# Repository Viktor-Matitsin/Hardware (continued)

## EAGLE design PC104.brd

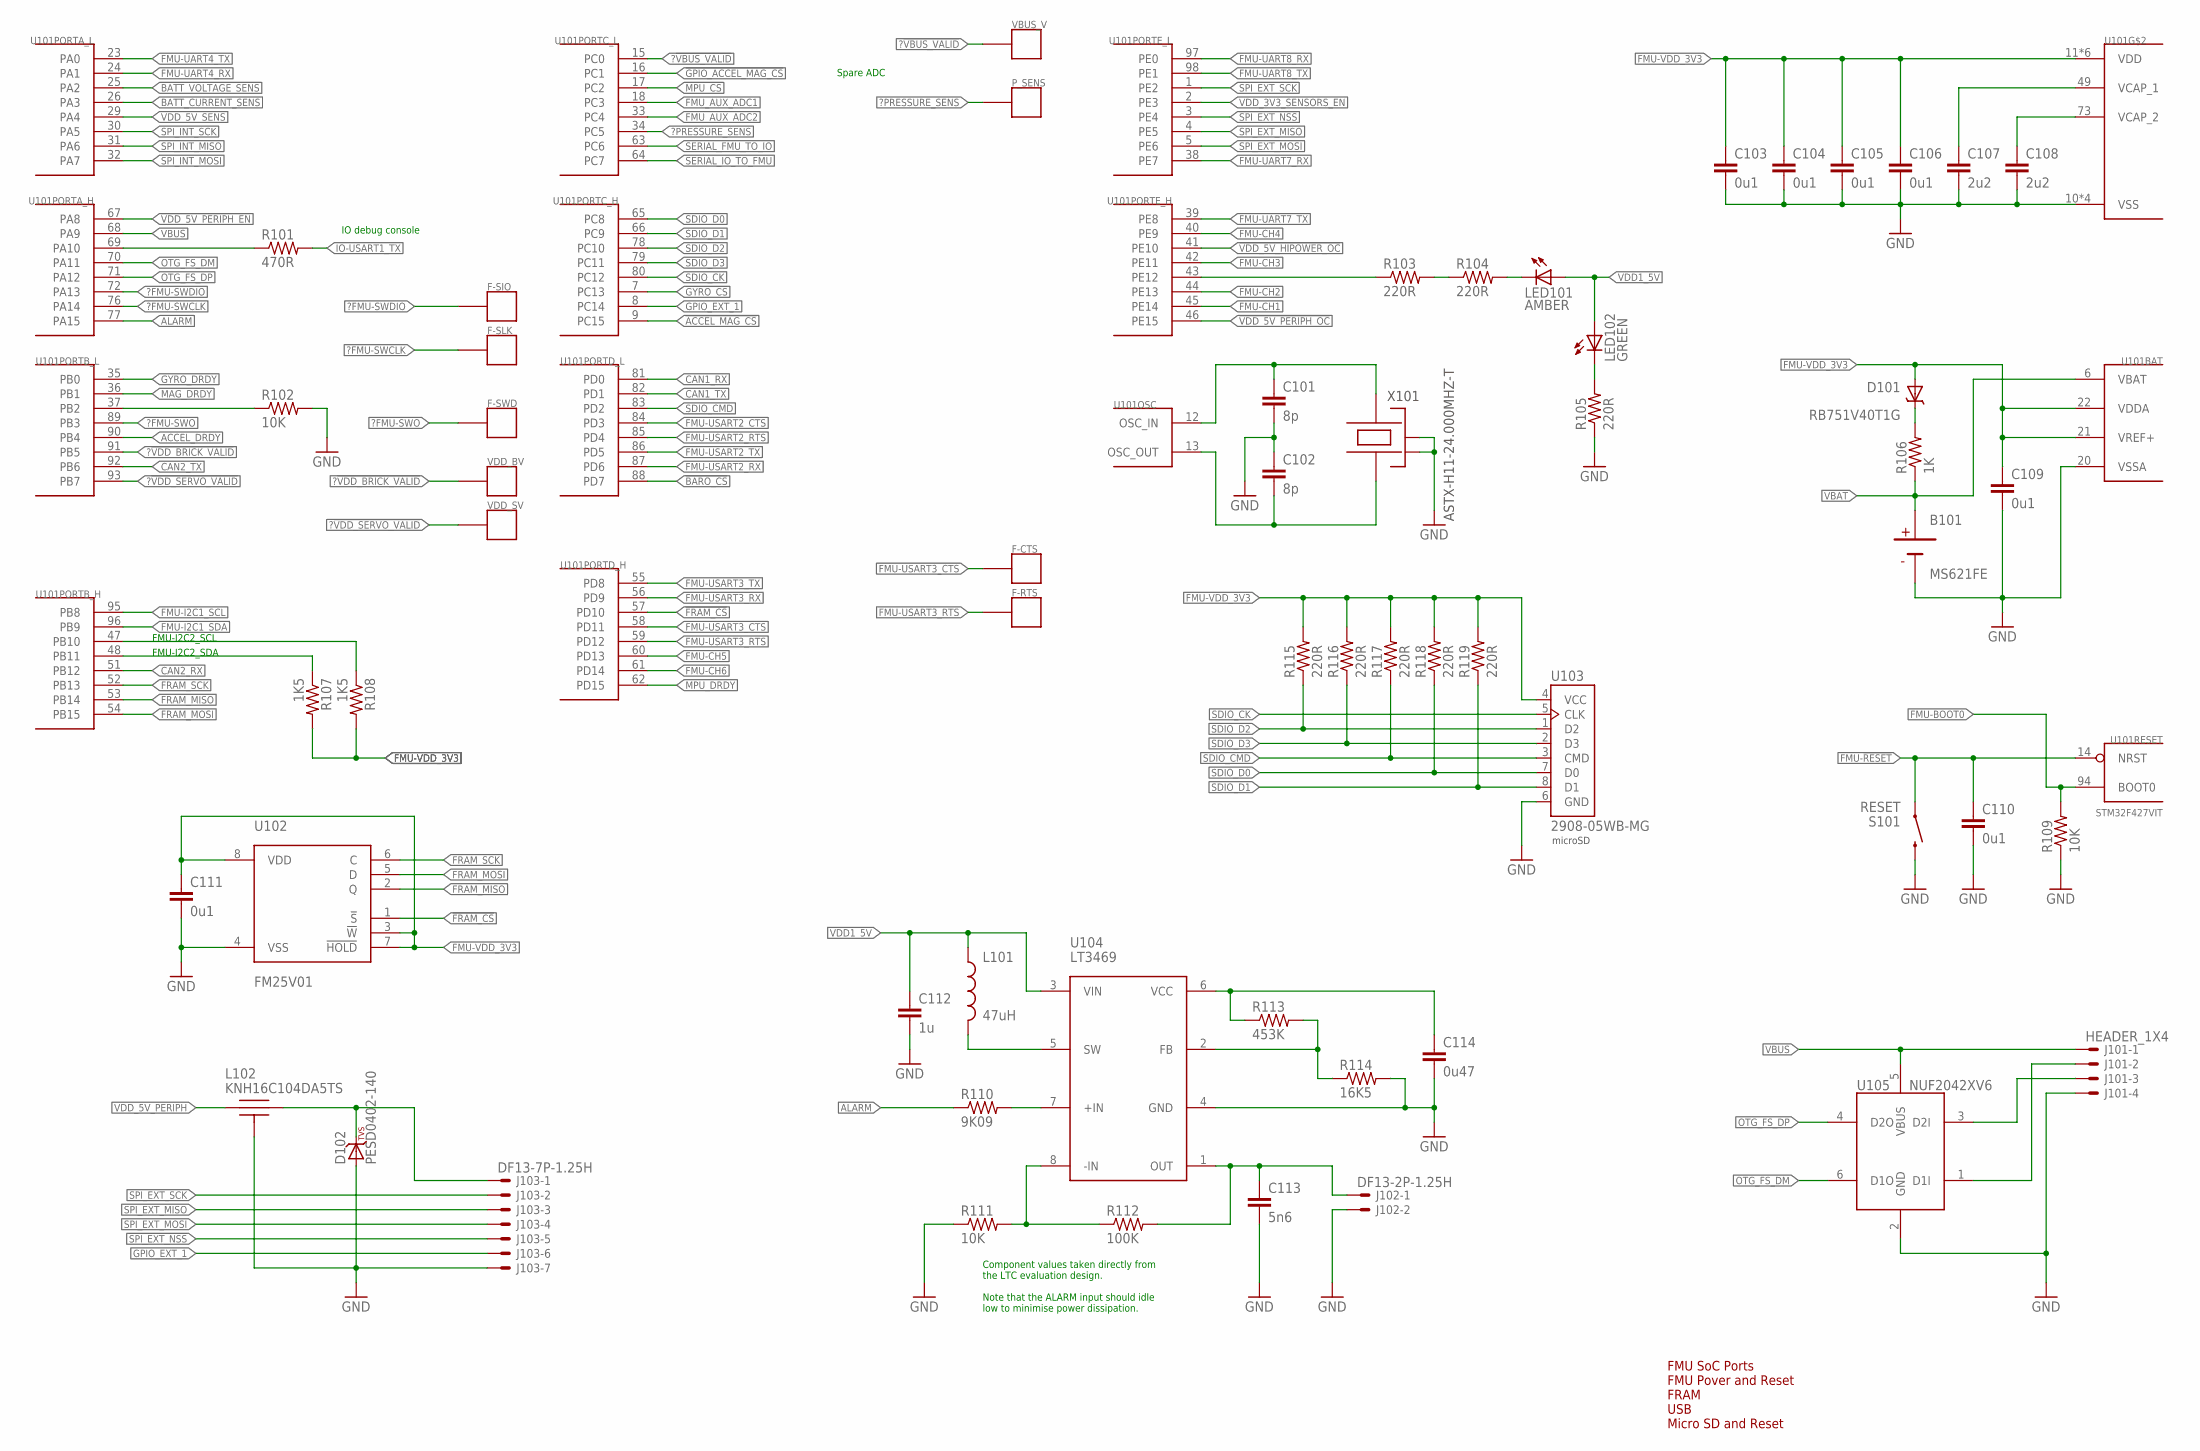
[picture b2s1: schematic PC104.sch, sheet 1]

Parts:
B101: MS621FE
C101, C102: 8p; 0603-CAP
C103, C104, C105, C106, C109, C110, C111: 0u1; 0603-CAP
C107, C108: 2u2; 0603-CAP
C112: 1u; 0603-CAP
C113: 5n6; 0603-CAP
C114: 0u47; 0603-CAP
D101: RB751V40T1G; SOD323
D102: PESD0402-140; 0402-TVS
F-CTS: PAD.04; PAD.04X.04
F-RTS: PAD.04; PAD.04X.04
F-SIO: PAD.04; PAD.04X.04
F-SLK: PAD.04; PAD.04X.04
F-SWD: PAD.04; PAD.04X.04
J101: HEADER_1X4; HEADER_2.54MM-1X04
J102: DF13-2P-1.25H; DF13A-2P-1.25H
J103: DF13-7P-1.25H; DF13A-7P-1.25H
L101: 47uH; 0805-IND
L102: KNH16C104DA5TS; KYOCERA-KNH16-DA
LED101: AMBER; 0603-LED
LED102: GREEN; 0603-LED
P_SENS: PAD.04; PAD.04X.04
R101: 470R; 0603-RES
R102, R109, R111: 10K; 0603-RES
R103, R104, R105, R115, R116, R117, R118, R119: 220R; 0603-RES
R106: 1K; 0603-RES
R107, R108: 1K5; 0603-RES
R110: 9K09; 0603-RES
R112: 100K; 0603-RES
R113: 453K; 0603-RES
R114: 16K5; 0603-RES
S101: RESET; EVQP7J01K
U101: STM32F427VIT; TQFP100
U102: FM25V01; SO08
U103: 2908-05WB-MG; MICROSD
U104: LT3469; SOT23-8
U105: NUF2042XV6; SOT563-6
VBUS_V: PAD.04; PAD.04X.04
VDD_BV: PAD.04; PAD.04X.04
VDD_SV: PAD.04; PAD.04X.04
X101: ASTX-H11-24.000MHZ-T; OSCILLATOR-3.2X2.5

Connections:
!ACCEL_MAG_CS: U101.9 (PC15); also elsewhere on the board
!BARO_CS: U101.88 (PD7); also elsewhere on the board
!FRAM_CS: U101.57 (PD10), U102.1 (!S)
!GPIO_ACCEL_MAG_CS: U101.16 (PC1); also elsewhere on the board
!GYRO_CS: U101.7 (PC13); also elsewhere on the board
!MPU_CS: U101.17 (PC2); also elsewhere on the board
!SPI_EXT_NSS: J103.5, U101.3 (PE4)
!VDD_5V_HIPOWER_OC: U101.41 (PE10); also elsewhere on the board
!VDD_5V_PERIPH_EN: U101.67 (PA8); also elsewhere on the board
!VDD_5V_PERIPH_OC: U101.46 (PE15); also elsewhere on the board
?!VBUS_VALID: U101.15 (PC0), VBUS_V.P$1
?!VDD_BRICK_VALID: U101.91 (PB5), VDD_BV.P$1
?!VDD_SERVO_VALID: U101.93 (PB7), VDD_SV.P$1
?FMU-SWCLK: F-SLK.P$1, U101.76 (PA14)
?FMU-SWDIO: F-SIO.P$1, U101.72 (PA13)
?FMU-SWO: F-SWD.P$1, U101.89 (PB3)
?PRESSURE_SENS: P_SENS.P$1, U101.34 (PC5)
ACCEL_DRDY: U101.90 (PB4); also elsewhere on the board
ALARM: R110.1, U101.77 (PA15)
BATT_CURRENT_SENS: U101.26 (PA3); also elsewhere on the board
BATT_VOLTAGE_SENS: U101.25 (PA2); also elsewhere on the board
CAN1_RX: U101.81 (PD0); also elsewhere on the board
CAN1_TX: U101.82 (PD1); also elsewhere on the board
CAN2_RX: U101.51 (PB12); also elsewhere on the board
CAN2_TX: U101.92 (PB6); also elsewhere on the board
FMU-!RESET: C110.P$1 (1), S101.A1 (1), U101.14 (NRST)
FMU-BOOT0: R109.2, U101.94 (BOOT0)
FMU-CH1: U101.45 (PE14); also elsewhere on the board
FMU-CH2: U101.44 (PE13); also elsewhere on the board
FMU-CH3: U101.42 (PE11); also elsewhere on the board
FMU-CH4: U101.40 (PE9); also elsewhere on the board
FMU-CH5: U101.60 (PD13); also elsewhere on the board
FMU-CH6: U101.61 (PD14); also elsewhere on the board
FMU-I2C1_SCL: U101.95 (PB8); also elsewhere on the board
FMU-I2C1_SDA: U101.96 (PB9); also elsewhere on the board
FMU-UART4_RX: U101.24 (PA1); also elsewhere on the board
FMU-UART4_TX: U101.23 (PA0); also elsewhere on the board
FMU-UART7_RX: U101.38 (PE7); also elsewhere on the board
FMU-UART7_TX: U101.39 (PE8); also elsewhere on the board
FMU-UART8_RX: U101.97 (PE0); also elsewhere on the board
FMU-UART8_TX: U101.98 (PE1); also elsewhere on the board
FMU-USART2_CTS: U101.84 (PD3); also elsewhere on the board
FMU-USART2_RTS: U101.85 (PD4); also elsewhere on the board
FMU-USART2_RX: U101.87 (PD6); also elsewhere on the board
FMU-USART2_TX: U101.86 (PD5); also elsewhere on the board
FMU-USART3_CTS: F-CTS.P$1, U101.58 (PD11)
FMU-USART3_RTS: F-RTS.P$1, U101.59 (PD12)
FMU-USART3_RX: U101.56 (PD9); also elsewhere on the board
FMU-USART3_TX: U101.55 (PD8); also elsewhere on the board
FMU-VDD_3V3: C103.P$1 (1), C104.P$1 (1), C105.P$1 (1), C106.P$1 (1), C109.P$1 (1), C111.P$1 (1), D101.A, R107.2, R108.2, R115.2, R116.2, R117.2, R118.2, R119.2, U101.11 (VDD), U101.19 (VDD), U101.21 (VREF+), U101.22 (VDDA), U101.28 (VDD), U101.50 (VDD), U101.75 (VDD), U101.100 (VDD), U102.3 (!W), U102.7 (!HOLD), U102.8 (VDD), U103.4 (VCC); also elsewhere on the board
FMU_AUX_ADC1: U101.18 (PC3); also elsewhere on the board
FMU_AUX_ADC2: U101.33 (PC4); also elsewhere on the board
FRAM_MISO: U101.53 (PB14), U102.2 (Q)
FRAM_MOSI: U101.54 (PB15), U102.5 (D)
FRAM_SCK: U101.52 (PB13), U102.6 (C)
GND: B101.2 (NEG), C101.P$2 (2), C102.P$1 (1), C103.P$2 (2), C104.P$2 (2), C105.P$2 (2), C106.P$2 (2), C107.P$2 (2), C108.P$2 (2), C109.P$2 (2), C110.P$2 (2), C111.P$2 (2), C112.P$2 (2), C113.P$2 (2), C114.P$2 (2), D102.A, J101.4, J102.2, J103.7, L102.P$3, L102.P$4, L102.P$5, R102.2, R105.1, R109.1, R111.1, R114.2, S101.B3 (2), U101.10 (VSS), U101.20 (VSSA), U101.27 (VSS), U101.74 (VSS), U101.99 (VSS), U102.4 (VSS), U103.6 (GND), U104.4 (GND), U105.2 (GND), X101.2 (NC_2), X101.4 (NC_4); also elsewhere on the board
GPIO_EXT_1: J103.6, U101.8 (PC14)
GYRO_DRDY: U101.35 (PB0); also elsewhere on the board
IO-USART1_TX: R101.2; also elsewhere on the board
MAG_DRDY: U101.36 (PB1); also elsewhere on the board
MPU_DRDY: U101.62 (PD15); also elsewhere on the board
unnamed: J101.3, U105.3 (D2I)
unnamed: C108.P$1 (1), U101.73 (VCAP_2)
unnamed: C102.P$2 (2), U101.13 (OSC_OUT), X101.1
unnamed: C101.P$1 (1), U101.12 (OSC_IN), X101.3
unnamed: C107.P$1 (1), U101.49 (VCAP_1)
unnamed: J101.2, U105.1 (D1I)
unnamed: R101.1, U101.69 (PA10)
unnamed: D101.C, R106.2
unnamed: R102.1, U101.37 (PB2)
unnamed: R103.1, U101.43 (PE12)
unnamed: C114.P$1 (1), R113.1, U104.6 (VCC)
unnamed: R113.2, R114.1, U104.2 (FB)
unnamed: L101.P$2 (2), U104.5 (SW)
unnamed: R103.2, R104.1
unnamed: LED101.C, R104.2
unnamed: LED102.C, R105.2
unnamed: R111.2, R112.1, U104.8 (-IN)
unnamed: C113.P$1 (1), J102.1, R112.2, U104.1 (OUT)
unnamed: R110.2, U104.7 (+IN)
unnamed: R108.1, U101.47 (PB10)
unnamed: R107.1, U101.48 (PB11)
unnamed: D102.C, J103.1, L102.P$2
OTG_FS_DM: U101.70 (PA11), U105.6 (D1O)
OTG_FS_DP: U101.71 (PA12), U105.4 (D2O)
SDIO_CK: U101.80 (PC12), U103.5 (CLK)
SDIO_CMD: R117.1, U101.83 (PD2), U103.3 (CMD)
SDIO_D0: R118.1, U101.65 (PC8), U103.7 (D0)
SDIO_D1: R119.1, U101.66 (PC9), U103.8 (D1)
SDIO_D2: R115.1, U101.78 (PC10), U103.1 (D2)
SDIO_D3: R116.1, U101.79 (PC11), U103.2 (D3)
SERIAL_FMU_TO_IO: U101.63 (PC6); also elsewhere on the board
SERIAL_IO_TO_FMU: U101.64 (PC7); also elsewhere on the board
SPI_EXT_MISO: J103.3, U101.4 (PE5)
SPI_EXT_MOSI: J103.4, U101.5 (PE6)
SPI_EXT_SCK: J103.2, U101.1 (PE2)
SPI_INT_MISO: U101.31 (PA6); also elsewhere on the board
SPI_INT_MOSI: U101.32 (PA7); also elsewhere on the board
SPI_INT_SCK: U101.30 (PA5); also elsewhere on the board
VBAT: B101.1 (POS), R106.1, U101.6 (VBAT); also elsewhere on the board
VBUS: J101.1, U101.68 (PA9), U105.5 (VBUS)
VDD1_5V: C112.P$1 (1), L101.P$1 (1), LED101.A, LED102.A, U104.3 (VIN); also elsewhere on the board
VDD_3V3_SENSORS_EN: U101.2 (PE3); also elsewhere on the board
VDD_5V_PERIPH: L102.P$1; also elsewhere on the board
VDD_5V_SENS: U101.29 (PA4); also elsewhere on the board

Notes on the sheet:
FMU SoC Ports FMU Pover and Reset FRAM USB Micro SD and Reset
Component values taken directly from the LTC evaluation design. Note that the ALARM input should idle low to minimise power dissipation.
FMU-I2C2_SCL
FMU-I2C2_SDA
Spare ADC
microSD
IO debug console

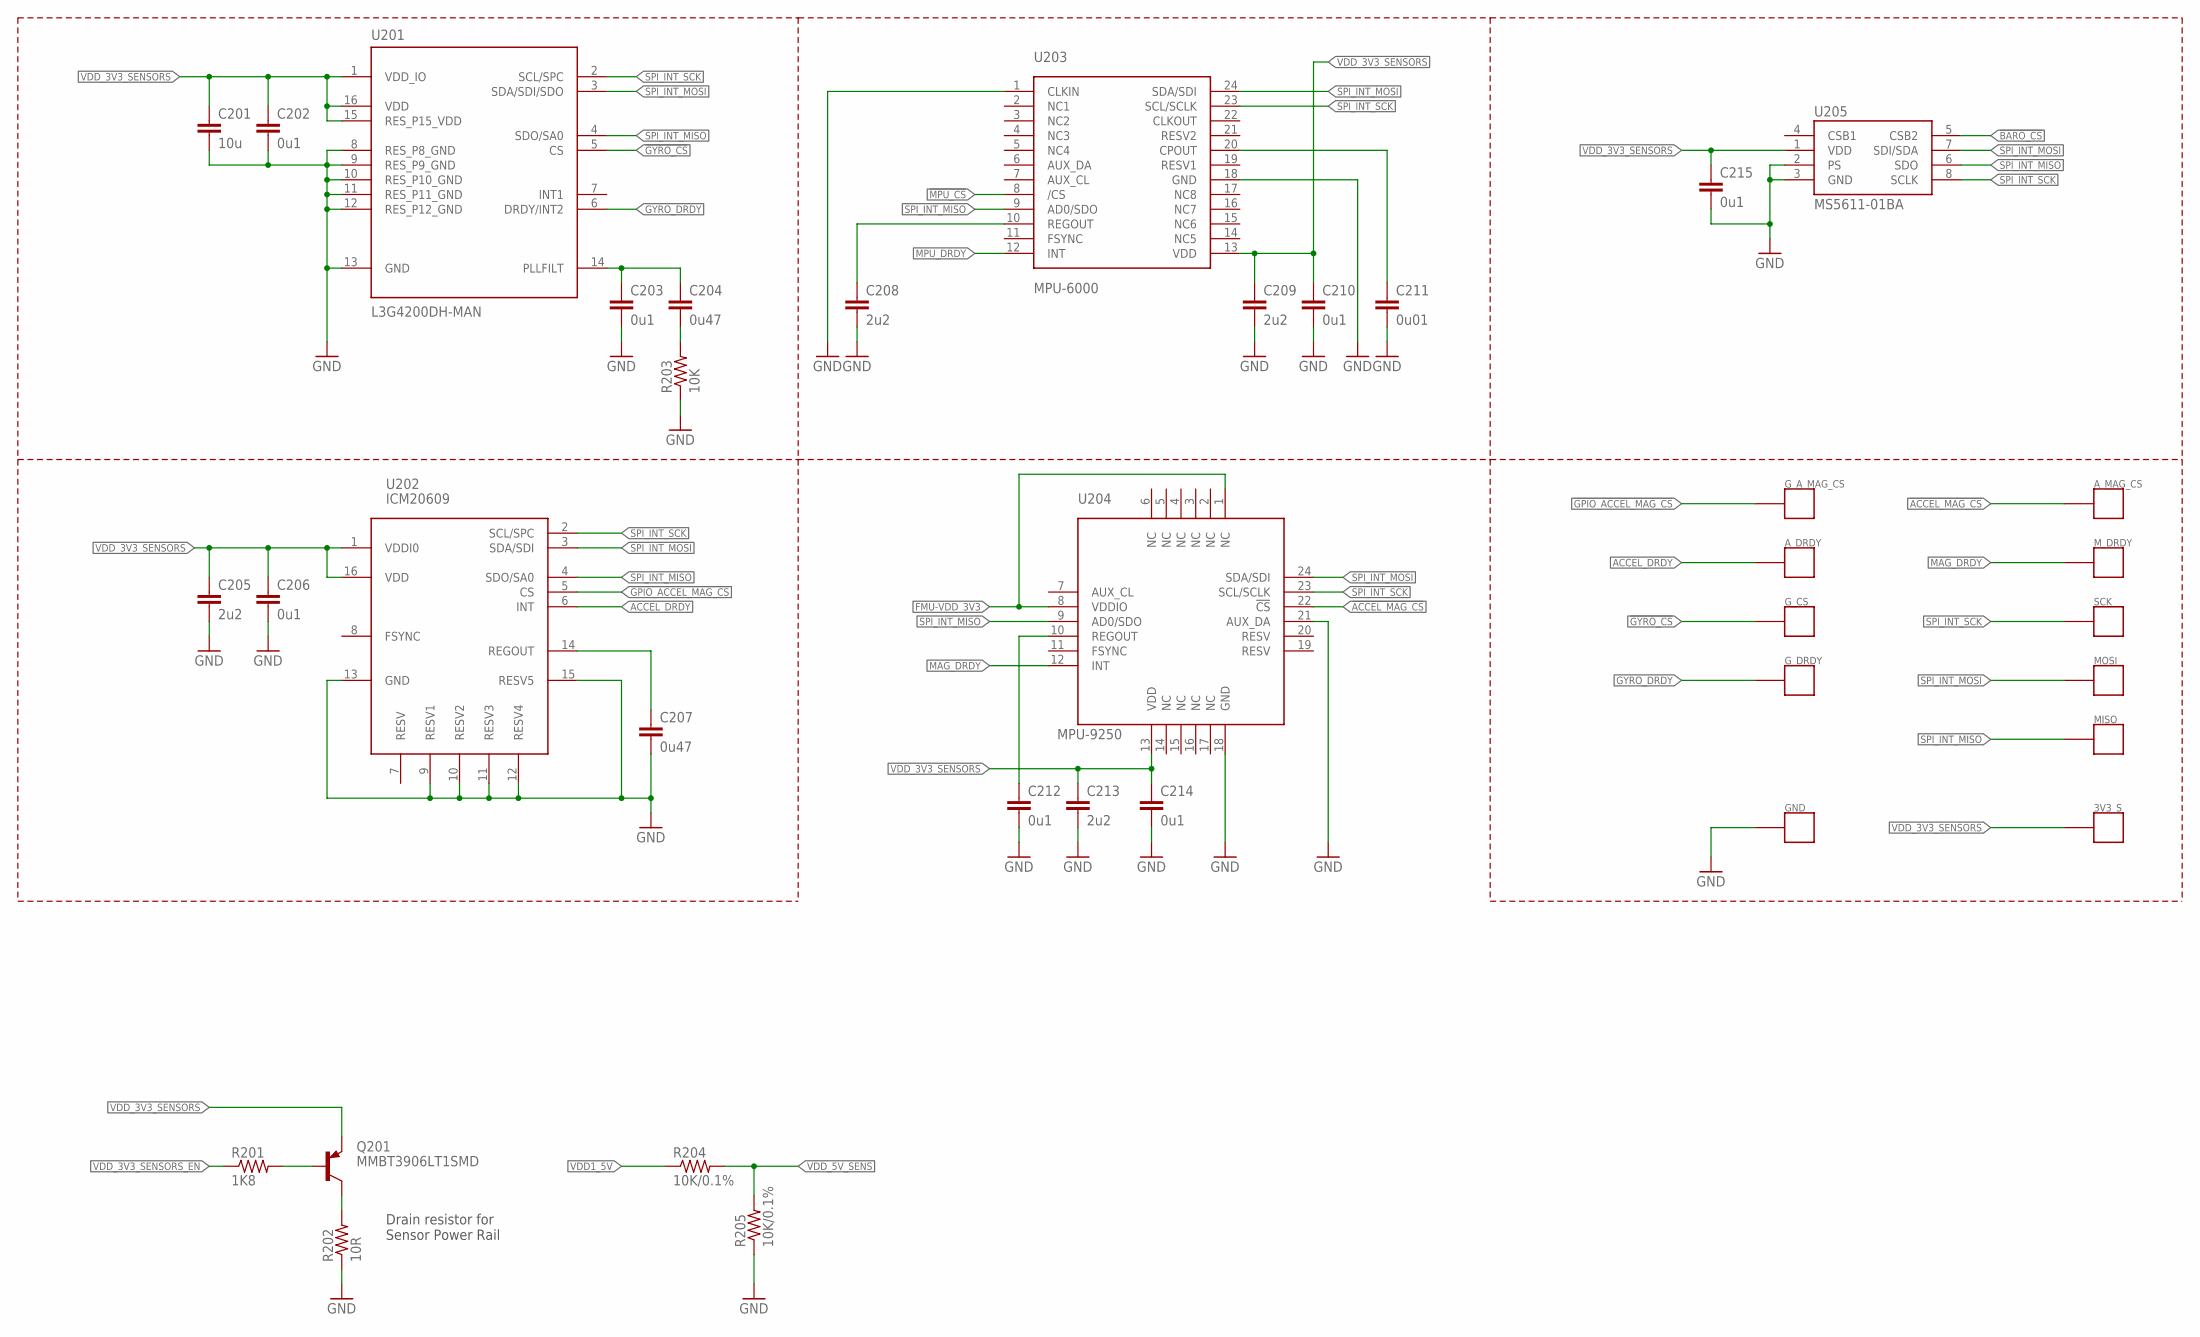
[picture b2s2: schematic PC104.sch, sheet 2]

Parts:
3V3_S: PAD.04; PAD.04X.04
A_DRDY: PAD.04; PAD.04X.04
A_MAG_CS: PAD.04; PAD.04X.04
C201: 10u; 0805-CAP
C202, C203, C206, C210, C212, C214, C215: 0u1; 0603-CAP
C204, C207: 0u47; 0603-CAP
C205, C208, C209, C213: 2u2; 0603-CAP
C211: 0u01; 0603-CAP
GND: PAD.04; PAD.04X.04
G_A_MAG_CS: PAD.04; PAD.04X.04
G_CS: PAD.04; PAD.04X.04
G_DRDY: PAD.04; PAD.04X.04
MISO: PAD.04; PAD.04X.04
MOSI: PAD.04; PAD.04X.04
M_DRDY: PAD.04; PAD.04X.04
Q201: MMBT3906LT1SMD; SOT23-BEC
R201: 1K8; 0603-RES
R202: 10R; 0603-RES
R203: 10K; 0603-RES
R204, R205: 10K/0.1%; 0603-RES
SCK: PAD.04; PAD.04X.04
U201: L3G4200DH-MAN
U202: ICM20609; LGA-16-3PX5P
U203: MPU-6000; QFN-24
U204: MPU-9250; MPU-6500
U205: MS5611-01BA

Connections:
!ACCEL_MAG_CS: A_MAG_CS.P$1, U204.22 (!CS); also elsewhere on the board
!BARO_CS: U205.5 (CSB2); also elsewhere on the board
!GPIO_ACCEL_MAG_CS: G_A_MAG_CS.P$1, U202.5 (CS); also elsewhere on the board
!GYRO_CS: G_CS.P$1, U201.5 (CS); also elsewhere on the board
!MPU_CS: U203.8 (/CS); also elsewhere on the board
ACCEL_DRDY: A_DRDY.P$1, U202.6 (INT); also elsewhere on the board
FMU-VDD_3V3: U204.1 (NC), U204.8 (VDDIO); also elsewhere on the board
GND: C201.P$2 (2), C202.P$2 (2), C203.P$2 (2), C205.P$2 (2), C206.P$2 (2), C207.P$2 (2), C208.P$2 (2), C209.P$2 (2), C210.P$2 (2), C211.P$2 (2), C212.P$2 (2), C213.P$2 (2), C214.P$2 (2), C215.P$2 (2), GND.P$1, R202.1, R203.1, R205.1, U201.8 (RES_P8_GND), U201.9 (RES_P9_GND), U201.10 (RES_P10_GND), U201.11 (RES_P11_GND), U201.12 (RES_P12_GND), U201.13 (GND), U202.9 (RESV1), U202.10 (RESV2), U202.11 (RESV3), U202.12 (RESV4), U202.13 (GND), U202.15 (RESV5), U203.1 (CLKIN), U203.18 (GND), U204.18 (GND), U204.21 (AUX_DA), U205.2 (PS), U205.3 (GND); also elsewhere on the board
GYRO_DRDY: G_DRDY.P$1, U201.6 (DRDY/INT2); also elsewhere on the board
MAG_DRDY: M_DRDY.P$1, U204.12 (INT); also elsewhere on the board
MPU_DRDY: U203.12 (INT); also elsewhere on the board
unnamed: C204.P$2 (2), R203.2
unnamed: Q201.B, R201.2
unnamed: Q201.C, R202.2
unnamed: C211.P$1 (1), U203.20 (CPOUT)
unnamed: C203.P$1 (1), C204.P$1 (1), U201.14 (PLLFILT)
unnamed: C208.P$1 (1), U203.10 (REGOUT)
unnamed: C212.P$1 (1), U204.10 (REGOUT)
unnamed: C207.P$1 (1), U202.14 (REGOUT)
SPI_INT_MISO: MISO.P$1, U201.4 (SDO/SA0), U202.4 (SDO/SA0), U203.9 (AD0/SDO), U204.9 (AD0/SDO), U205.6 (SDO); also elsewhere on the board
SPI_INT_MOSI: MOSI.P$1, U201.3 (SDA/SDI/SDO), U202.3 (SDA/SDI), U203.24 (SDA/SDI), U204.24 (SDA/SDI), U205.7 (SDI/SDA); also elsewhere on the board
SPI_INT_SCK: SCK.P$1, U201.2 (SCL/SPC), U202.2 (SCL/SPC), U203.23 (SCL/SCLK), U204.23 (SCL/SCLK), U205.8 (SCLK); also elsewhere on the board
VDD1_5V: R204.1; also elsewhere on the board
VDD_3V3_SENSORS: 3V3_S.P$1, C201.P$1 (1), C202.P$1 (1), C205.P$1 (1), C206.P$1 (1), C209.P$1 (1), C210.P$1 (1), C213.P$1 (1), C214.P$1 (1), C215.P$1 (1), Q201.E, U201.1 (VDD_IO), U201.15 (RES_P15_VDD), U201.16 (VDD), U202.1 (VDDI0), U202.16 (VDD), U203.13 (VDD), U204.13 (VDD), U205.1 (VDD); also elsewhere on the board
VDD_3V3_SENSORS_EN: R201.1; also elsewhere on the board
VDD_5V_SENS: R204.2, R205.2; also elsewhere on the board

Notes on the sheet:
Drain resistor for Sensor Power Rail

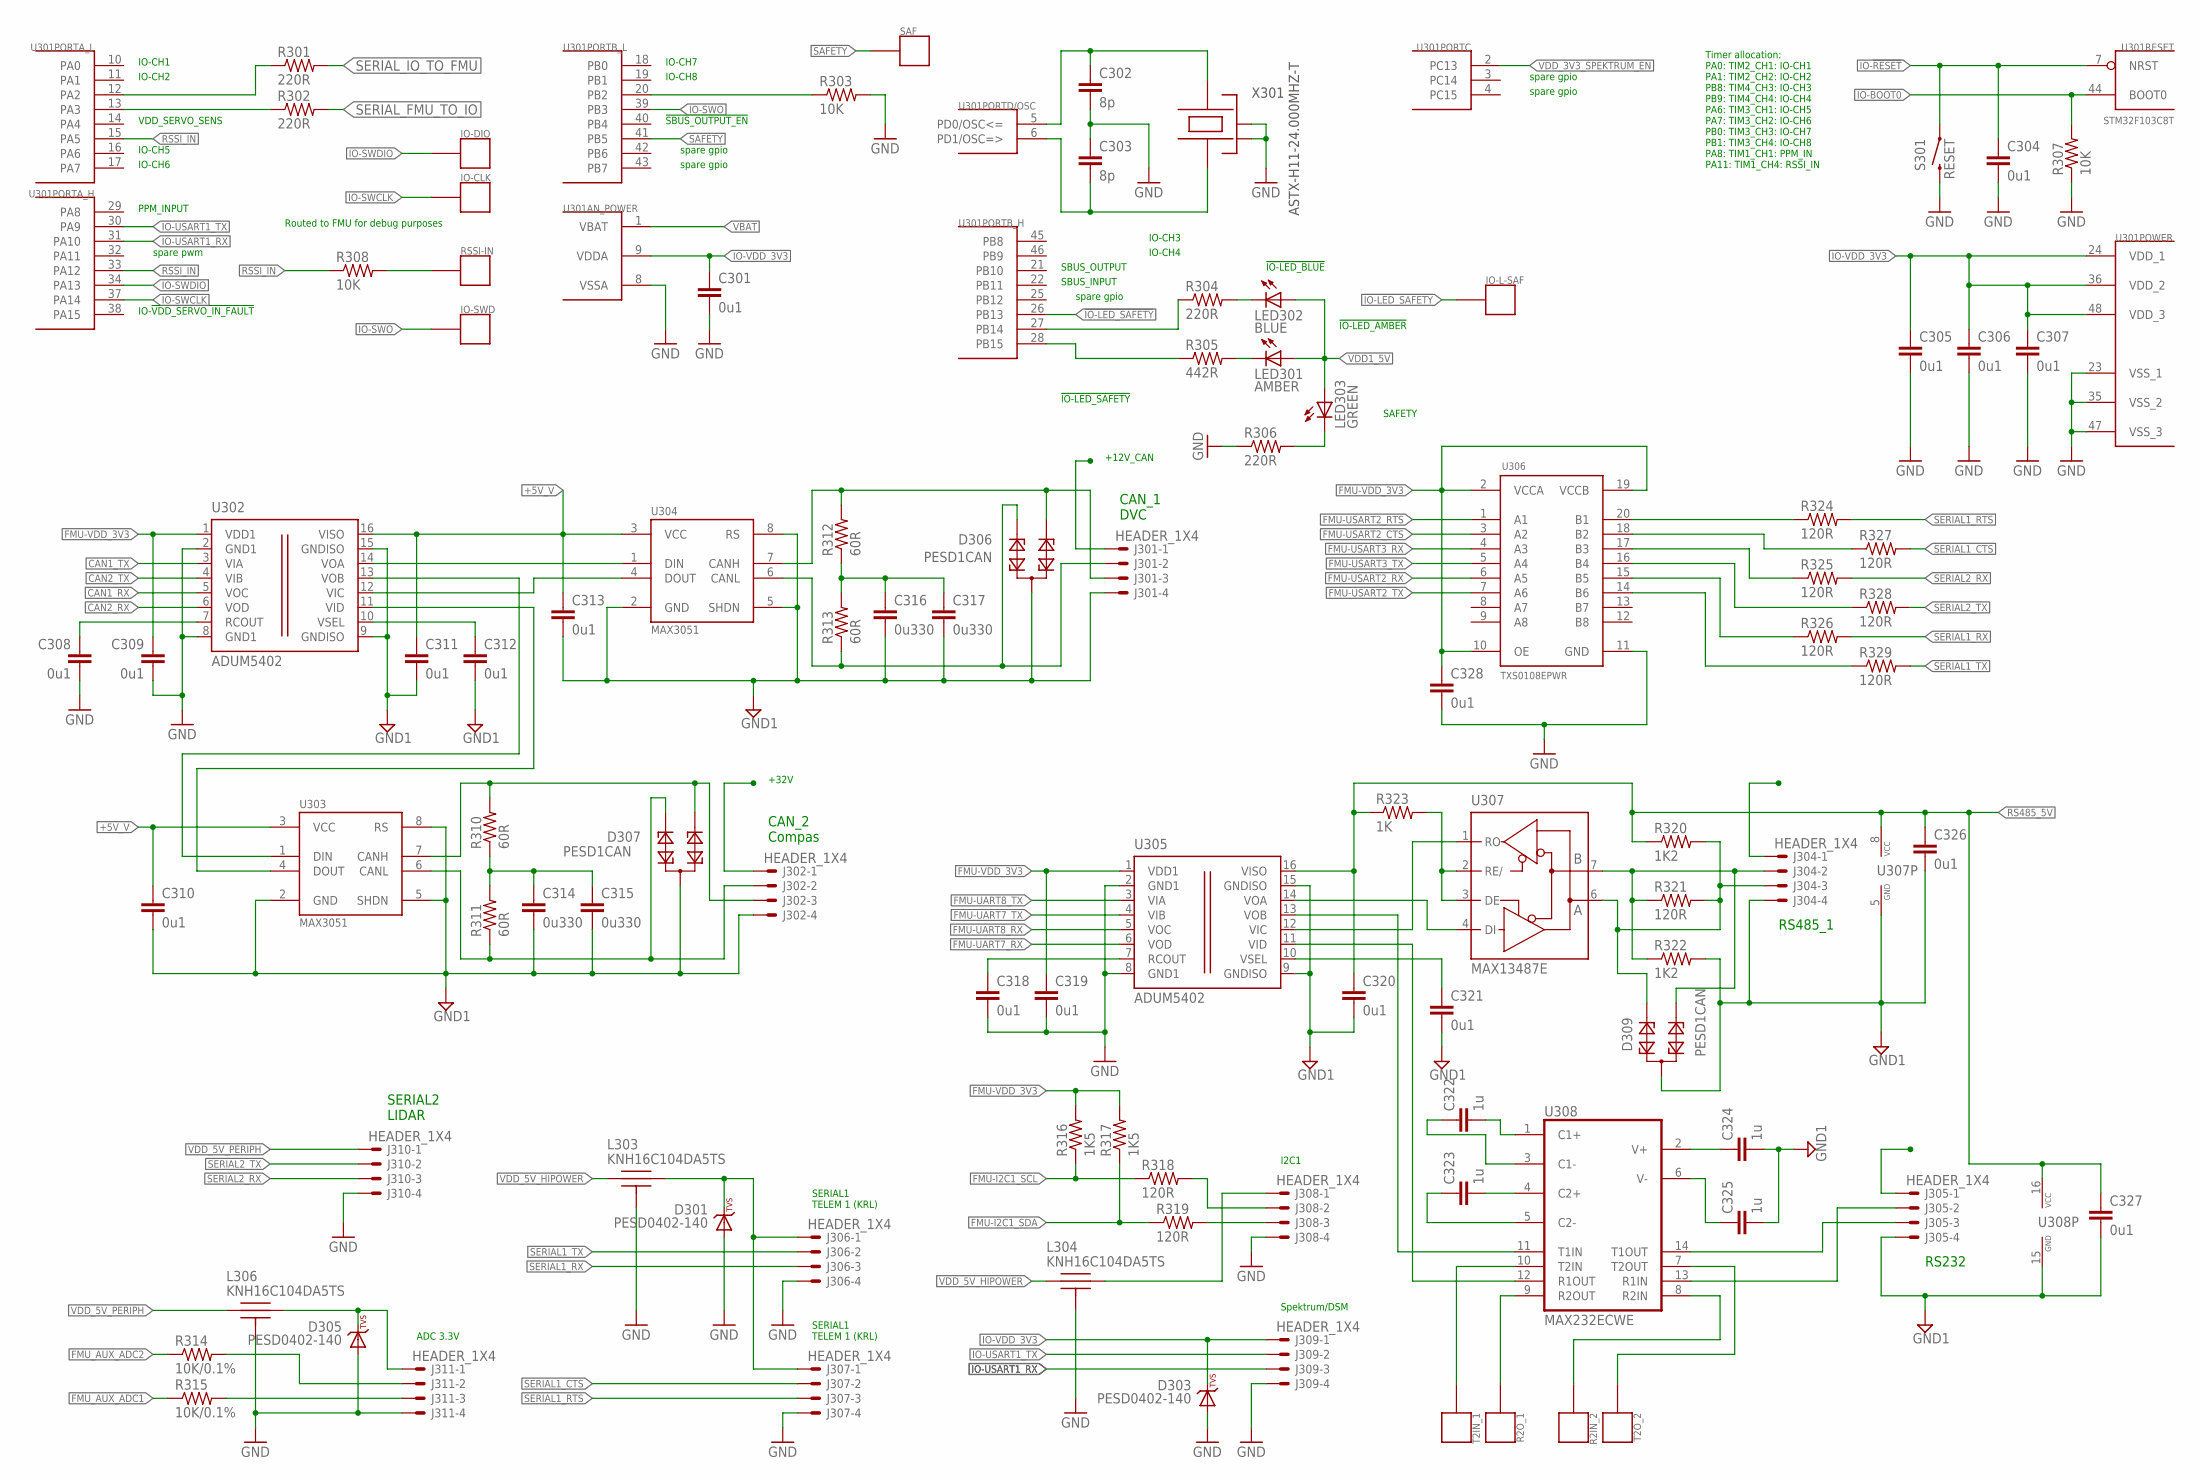
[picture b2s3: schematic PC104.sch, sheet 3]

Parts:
C301, C304, C305, C306, C307, C308, C309, C310, C311, C312, C313, C318, C319, C320, C321, C326, C327, C328: 0u1; 0603-CAP
C302, C303: 8p; 0603-CAP
C314, C315, C316, C317: 0u330; 1210
C322, C323, C324, C325: 1u; 0603-CAP
D301, D303, D305: PESD0402-140; 0402-TVS
D306, D307, D309: PESD1CAN; SOT23@1
IO-CLK: PAD.04; PAD.04X.04
IO-DIO: TP31; PAD.04X.04
IO-L-SAF: PAD.04; PAD.04X.04
IO-SWD: PAD.04; PAD.04X.04
J301, J302, J304, J305, J306, J307, J308, J309, J310, J311: HEADER_1X4; HEADER_2.54MM-1X04
L303, L304, L306: KNH16C104DA5TS; KYOCERA-KNH16-DA
LED301: AMBER; 0603-LED
LED302: BLUE; 0603-LED
LED303: GREEN; 0603-LED
R2IN_2, R2O_1: PAD.04; PAD.04X.04
R301, R302, R304, R306: 220R; 0603-RES
R303, R307, R308: 10K; 0603-RES
R305: 442R; 0603-RES
R310, R311, R312, R313: 60R; 0603-RES
R314, R315: 10K/0.1%; 0603-RES
R316, R317: 1K5; 0603-RES
R318, R319, R321, R324, R325, R326, R327, R328, R329: 120R; 0603-RES
R320, R322: 1K2; 0603-RES
R323: 1K; 0603-RES
RSSI-IN: PAD.04; PAD.04X.04
S301: RESET; EVQP7J01K
SAF: PAD.04; PAD.04X.04
T2IN_1: T2IN; PAD.04X.04
T2O_2: PAD.04; PAD.04X.04
U301: STM32F103C8T; TQFP48
U302, U305: ADUM5402; SO-16W
U303, U304: MAX3051; SO08
U306: TXS0108EPWR; R-PDSO-G20
U307: MAX13487E; SO08
U308: MAX232ECWE; SO16L
X301: ASTX-H11-24.000MHZ-T; OSCILLATOR-3.2X2.5

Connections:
!IO-LED_SAFETY: IO-L-SAF.P$1, U301.26 (PB13)
+5V: J305.1
+5V_V: C310.P$1 (1), C311.P$1 (1), C313.P$1 (1), U302.16 (VISO), U303.3 (VCC), U304.3 (VCC)
+12V: J304.1
+12V_CAN: J301.1
+32V_CAN: J302.1
CAN1_RX: U302.5 (VOC); also elsewhere on the board
CAN1_TX: U302.3 (VIA); also elsewhere on the board
CAN2_RX: U302.6 (VOD); also elsewhere on the board
CAN2_RX_IN: U302.11 (VID), U303.4 (DOUT)
CAN2_TX: U302.4 (VIB); also elsewhere on the board
CAN2_TX_IN: U302.13 (VOB), U303.1 (DIN)
FMU-I2C1_SCL: R316.1, R318.1; also elsewhere on the board
FMU-I2C1_SDA: R317.1, R319.1; also elsewhere on the board
FMU-UART7_RX: U305.6 (VOD); also elsewhere on the board
FMU-UART7_TX: U305.4 (VIB); also elsewhere on the board
FMU-UART8_RX: U305.5 (VOC); also elsewhere on the board
FMU-UART8_TX: U305.3 (VIA); also elsewhere on the board
FMU-USART2_CTS: U306.3 (A2); also elsewhere on the board
FMU-USART2_RTS: U306.1 (A1); also elsewhere on the board
FMU-USART2_RX: U306.6 (A5); also elsewhere on the board
FMU-USART2_TX: U306.7 (A6); also elsewhere on the board
FMU-USART3_RX: U306.4 (A3); also elsewhere on the board
FMU-USART3_TX: U306.5 (A4); also elsewhere on the board
FMU-VDD_3V3: C309.P$1 (1), C319.P$1 (1), C328.P$1 (1), R316.2, R317.2, U302.1 (VDD1), U305.1 (VDD1), U306.2 (VCCA), U306.10 (OE), U306.19 (VCCB); also elsewhere on the board
FMU_AUX_ADC1: R315.1; also elsewhere on the board
FMU_AUX_ADC2: R314.1; also elsewhere on the board
GND: C301.P$2 (2), C302.P$2 (2), C303.P$1 (1), C304.P$2 (2), C305.P$2 (2), C306.P$2 (2), C307.P$2 (2), C308.P$2 (2), C309.P$2 (2), C318.P$2 (2), C319.P$2 (2), C328.P$2 (2), D301.A, D303.A, D305.A, J306.4, J307.4, J308.4, J309.4, J310.4, J311.4, L303.P$3, L303.P$4, L303.P$5, L304.P$3, L304.P$4, L304.P$5, L306.P$3, L306.P$4, L306.P$5, R303.2, R306.1, R307.1, S301.B3 (2), U301.8 (VSSA), U301.23 (VSS_1), U301.35 (VSS_2), U301.47 (VSS_3), U302.2 (GND1), U302.8 (GND1), U305.2 (GND1), U305.8 (GND1), U306.11 (GND), X301.2 (NC_2), X301.4 (NC_4); also elsewhere on the board
GND1: C310.P$2 (2), C311.P$2 (2), C312.P$2 (2), C313.P$2 (2), C314.2, C315.2, C316.2, C317.2, C320.P$2 (2), C321.P$2 (2), C324.P$2 (2), C325.P$2 (2), C326.P$2 (2), C327.P$2 (2), D306.3, D307.3, D309.3, J301.4, J302.4, J304.4, J305.4, R322.2, U302.9 (GNDISO), U302.15 (GNDISO), U303.2 (GND), U303.5 (SHDN), U303.8 (RS), U304.2 (GND), U304.5 (SHDN), U304.8 (RS), U305.9 (GNDISO), U305.15 (GNDISO), U307.5 (GND), U308.15 (GND)
IO-!RESET: C304.P$1 (1), S301.A1 (1), U301.7 (NRST)
IO-BOOT0: R307.2, U301.44 (BOOT0)
IO-SWCLK: IO-CLK.P$1, U301.37 (PA14)
IO-SWDIO: IO-DIO.P$1, U301.34 (PA13)
IO-SWO: IO-SWD.P$1, U301.39 (PB3)
IO-USART1_RX: J309.3, U301.31 (PA10)
IO-USART1_TX: J309.2, U301.30 (PA9); also elsewhere on the board
IO-VDD_3V3: C301.P$1 (1), C305.P$1 (1), C306.P$1 (1), C307.P$1 (1), D303.C, J309.1, U301.9 (VDDA), U301.24 (VDD_1), U301.36 (VDD_2), U301.48 (VDD_3); also elsewhere on the board
unnamed: R301.1, U301.12 (PA2)
unnamed: R302.1, U301.13 (PA3)
unnamed: R303.1, U301.20 (PB2)
unnamed: C303.P$2 (2), U301.6 (PD1/OSC=>), X301.1
unnamed: D309.1, J304.3, R320.2, R321.2, U307.6 (A)
unnamed: J305.2, U308.13 (R1IN)
unnamed: D309.2, J304.2, R321.1, R322.1, U307.7 (B)
unnamed: R308.2, RSSI-IN.P$1
unnamed: C308.P$1 (1), U302.7 (RCOUT)
unnamed: LED303.C, R306.2
unnamed: J311.3, R315.2
unnamed: C312.P$1 (1), U302.10 (VSEL)
unnamed: D301.C, J306.1, J307.1, L303.P$2
unnamed: C323.P$2 (2), U308.4 (C2+)
unnamed: R304.1, U301.27 (PB14)
unnamed: C316.1, C317.1, R312.1, R313.2
unnamed: J308.2, R318.2
unnamed: C323.P$1 (1), U308.5 (C2-)
unnamed: LED301.C, R305.2
unnamed: J308.3, R319.2
unnamed: R305.1, U301.28 (PB15)
unnamed: LED302.C, R304.2
unnamed: R328.1, U306.16 (B4)
unnamed: R326.1, U306.15 (B5)
unnamed: C322.P$2 (2), U308.1 (C1+)
unnamed: C322.P$1 (1), U308.3 (C1-)
unnamed: J305.3, U308.14 (T1OUT)
unnamed: J308.1, L304.P$2
unnamed: D305.C, J311.1, L306.P$2
unnamed: R325.1, U306.17 (B3)
unnamed: R327.1, U306.18 (B2)
unnamed: C318.P$1 (1), U305.7 (RCOUT)
unnamed: R329.1, U306.14 (B6)
unnamed: R324.1, U306.20 (B1)
unnamed: J311.2, R314.2
unnamed: C321.P$1 (1), U305.10 (VSEL)
unnamed: C324.P$1 (1), U308.2 (V+)
unnamed: C314.1, C315.1, R310.1, R311.2
unnamed: D306.1, J301.2, R313.1, U304.6 (CANL)
unnamed: D306.2, J301.3, R312.2, U304.7 (CANH)
unnamed: D307.1, J302.3, R310.2, U303.7 (CANH)
unnamed: D307.2, J302.2, R311.1, U303.6 (CANL)
unnamed: C325.P$1 (1), U308.6 (V-)
unnamed: R323.2, U307.2 (RE/), U307.3 (DE)
unnamed: T2IN_1.P$1, U308.10 (T2IN)
unnamed: R2O_1.P$1, U308.9 (R2OUT)
unnamed: T2O_2.P$1, U308.7 (T2OUT)
unnamed: R2IN_2.P$1, U308.8 (R2IN)
unnamed: U302.14 (VOA), U304.1 (DIN)
unnamed: U302.12 (VIC), U304.4 (DOUT)
RS485_5V: C320.P$1 (1), C326.P$1 (1), C327.P$1 (1), R320.1, R323.1, U305.16 (VISO), U307.8 (VCC), U308.16 (VCC)
RSSI_IN: R308.1, U301.15 (PA5), U301.33 (PA12)
SAFETY: SAF.P$1, U301.41 (PB5)
SERIAL1_CTS: J307.2, R327.2
SERIAL1_RTS: J307.3, R324.2
SERIAL1_RX: J306.3, R326.2
SERIAL1_TX: J306.2, R329.2
SERIAL2_RX: J310.3, R325.2
SERIAL2_TX: J310.2, R328.2
SERIAL_FMU_TO_IO: R302.2; also elsewhere on the board
SERIAL_IO_TO_FMU: R301.2; also elsewhere on the board
VBAT: U301.1 (VBAT); also elsewhere on the board
VDD1_5V: LED301.A, LED302.A, LED303.A; also elsewhere on the board
VDD_3V3_SPEKTRUM_EN: U301.2 (PC13)
VDD_5V_HIPOWER: L303.P$1, L304.P$1; also elsewhere on the board
VDD_5V_PERIPH: J310.1, L306.P$1; also elsewhere on the board
VIC: U305.12 (VIC), U307.1 (RO)
VID: U305.11 (VID), U308.12 (R1OUT)
VOA: U305.14 (VOA), U307.4 (DI)
VOB: U305.13 (VOB), U308.11 (T1IN)
X301: C302.P$1 (1), U301.5 (PD0/OSC<=), X301.3

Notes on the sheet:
spare gpio
spare pwm
Timer allocation: PA0: TIM2_CH1: IO-CH1 PA1: TIM2_CH2: IO-CH2 PB8: TIM4_CH3: IO-CH3 PB9: TIM4_CH4: IO-CH4 PA6: TIM3_CH1: IO-CH5 PA7: TIM3_CH2: IO-CH6 PB0: TIM3_CH3: IO-CH7 PB1: TIM3_CH4: IO-CH8 PA8: TIM1_CH1: PPM_IN PA11: TIM1_CH4: RSSI_IN
Routed to FMU for debug purposes
Spektrum/DSM
I2C1
SERIAL1 TELEM 1 (KRL)
ADC 3.3V
IO-CH1
IO-CH2
IO-CH5
IO-CH6
VDD_SERVO_SENS
PPM_INPUT
IO-!VDD_SERVO_IN_FAULT
IO-CH7
IO-CH8
!SBUS_OUTPUT_EN
IO-CH3
IO-CH4
SBUS_OUTPUT
SBUS_INPUT
!IO-LED_SAFETY
!IO-LED_BLUE
!IO-LED_AMBER
SAFETY
CAN_1 DVC
CAN_2 Compas
RS485_1
RS232
SERIAL2 LIDAR
+12V_CAN
+32V
